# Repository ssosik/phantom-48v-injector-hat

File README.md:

# Phantom 48V Injector HAT

A Raspberry Pi add-on board that generates **+48V phantom power** from the Pi's 5V GPIO rail and
injects it onto two balanced microphone lines feeding a **HiFiBerry DAC2 ADC Pro**. It was designed
for a stereo wildlife-recording rig (Pi 4B + HiFiBerry + ESP P93 preamps with Primo EM272 capsules)
but works for any pair of P48 mics into that ADC.

| Top (3D render) | Bottom (3D render) |
|---|---|
|  |  |

> **Status: v2 (2026-10-29). Design complete, not yet fabricated or tested.** Read
> [Known issues](#known-issues) before ordering boards: items 1–3 are open design questions.

## Specs

| | |
|---|---|
| Input | 5V from Pi GPIO pins 2/4, through a π input filter (C6/C8 – L2 – C1) |
| Converter | Analog Devices LT8362 boost, 404 kHz, Burst + spread-spectrum (SSFM) mode |
| Output | 47.6 V typ (46.0–49.3 V worst case), within IEC 61938 P48 (48 V ± 4 V) |
| Load budget | 16 mA at 48 V → ~185 mA from the Pi 5V rail |
| Injection | 6.81 kΩ 0.1% per leg, 2 channels, one SPDT switch for both, green LED indicator |
| DC block | 2.2 µF / 100 V X7R per leg (~15 Hz corner after DC-bias derating) |
| Connectors | J1 2×20 GPIO socket (bottom side), J2 2×3 to HiFiBerry J4, J3/J4 1×3 XLR pigtails |
| Board | 65 × 45 mm, 2-layer, 2× M2.5 mounting holes, all SMD passives 0805 or larger |

```
Pi 5V ─► π filter ─► LT8362 boost ─► FB1 + output caps ─► SW1 ─► 6.81k ×4 ─► XLR pins 2/3 (J3, J4)
                                                                                  │
                                                     HiFiBerry J4 (J2) ◄─ 2.2µF ×4 ┘
```

See [DESIGN_DOC.md](DESIGN_DOC.md) for the full rationale: why it's non-isolated, why 400 kHz,
resistor matching and CMRR, layout strategy, and hand-assembly and first-power procedures.

## Known issues

Items 1–3 are deferred design questions. Resolve them before fabrication; [TODO.md](TODO.md)
tracks them with the remaining verification steps.

1. **Phantom switching transients reach the HiFiBerry inputs.** The DC-block caps C13–C16
   start uncharged. When SW1 switches phantom on, the ADC side of each cap jumps with the line
   side. A rough estimate (6.81 kΩ feed into the PCM1863's ~8 kΩ input) gives about +26 V
   common-mode at the input pins, decaying with τ ≈ 30 ms. Switching off gives the mirror image
   (≈ −26 V); the active drain to GND doesn't prevent it. Typical mic-preamp phantom inputs put
   clamp diodes and a series resistor after the DC-block cap for this reason. Whether the
   HiFiBerry DAC2 ADC Pro already protects its inputs hasn't been checked. Until it is, switch
   phantom only with the ADC unpowered, or add a clamp per leg (series R + BAV99 to the rails,
   or a low-capacitance TVS). See PLAN #36.
2. **Stack order is undecided.** DESIGN_DOC says Pi → HiFiBerry → this HAT. PLAN #1 says
   Pi → this HAT → HiFiBerry. J1 is a bottom-side socket with no pass-through pins, so in the
   PLAN #1 order the HiFiBerry would get no GPIO (I²S/I²C). In the DESIGN_DOC order the J1 socket
   needs male pins on the HiFiBerry to mate with. Confirm the stack physically before ordering. See PLAN #37.
3. **J2 orientation.** J2 is a top-side vertical header (PLAN #7 asked for bottom side). If it
   connects to the HiFiBerry J4 through a 2×3 IDC ribbon, the ribbon swaps the odd and even rows.
   Check the pin-1 mapping end to end, since this is the only thing keeping L/R polarity right. See PLAN #38.
4. **Schematic is label-only.** Connectivity is generated by `wire_schematic.py` as net labels
   on unwired symbols. It is correct (ERC 0 errors), and v2 hides the footprint, datasheet and
   description fields, but it still reads as a parts list rather than a circuit diagram.
5. **SW1 slide direction isn't marked.** The silkscreen labels the switch "P48" and the LED
   "ON" rather than marking ON/OFF ends, because which slider position connects the
   common to pin 1 hasn't been verified against the C&K datasheet.

## Repository layout

| Path | What |
|---|---|
| `phantom-injector-hat.kicad_pro/.kicad_sch/.kicad_pcb` | KiCad 10 project |
| `phantom-injector-hat.kicad_dru` | Custom DRC rules (MSOP-16 clearance, power widths, SW-node isolation) |
| `BOM.csv` | Authoritative BOM with manufacturer and DigiKey part numbers |
| `digikey-order-5units.csv` | DigiKey bulk-order upload for 5 boards (+ spares) |
| `DESIGN_DOC.md` | Architecture, BOM rationale, netlist, layout and assembly notes |
| `PLAN.md` | Numbered design-review log (✅ = closed) |
| `TODO.md` | Open items before fabrication |
| `make_fab.sh` | DRC gate, then Gerbers, drill, pick-and-place and BOM into `fab/` |
| `ROUTING_GUIDE.md` | Pre-routing guide: trace widths per net, loop priorities |
| `TESTS.md` | How to run DRC/ERC/netlist checks and the simulations |
| `wire_schematic.py` | Generates schematic net labels from a Python `NETLIST` dict |
| `place_components.py` | Places PCB footprints from a `PLACEMENTS` dict |
| `check_netlist.py` + `netlist_golden.json` | Detects PCB net drift against a saved golden |
| `sims/` | ngspice decks and stdlib-Python models (boost, input filter, audio path) |
| `phantom-injector-hat.pretty/` | Project footprint library: LT8362 MSOP-16-EP (`MSE_16A_ADI`, from Ultra Librarian) and the `Logo_Sosik` silkscreen logo |
| `logo.kicad_sym` | Logo as a schematic symbol (source for the footprint) |
| `DRC.rpt`, `ERC.rpt` | Latest check reports |

`phantom-injector-hat-BOM.xlsx` is an early (2026-05-12) BOM snapshot. Use `BOM.csv`.

## Working with the project

Requires KiCad 10. The Python scripts need KiCad's bundled interpreter, which provides `pcbnew`.
The paths below are for macOS:

```bash
KPY=/Applications/KiCad/KiCad.app/Contents/Frameworks/Python.framework/Versions/3.9/bin/python3
KCLI=/Applications/KiCad/KiCad.app/Contents/MacOS/kicad-cli

$KCLI pcb drc --format report --all-track-errors -o DRC.rpt phantom-injector-hat.kicad_pcb
$KCLI sch erc -o ERC.rpt phantom-injector-hat.kicad_sch
$KPY check_netlist.py
```

Current baseline: DRC 0 violations and 0 unconnected (one `track_width` exception is excluded
in the project file, with its reason); ERC 0 errors and 13 warnings, all from the vendor
symbol's pin types. See [TESTS.md](TESTS.md).

## Ordering and assembly

- `./make_fab.sh` runs DRC with schematic parity, then writes `fab/phantom-injector-hat-v2-gerbers.zip`
  (Gerbers + Excellon), `fab/phantom-injector-hat-pos.csv` and a BOM copy. `fab/` is gitignored.
- `BOM.csv` is the source of truth. L1 (Coilcraft XAL5050-223MEC) isn't stocked at DigiKey;
  order it from coilcraft.com.
- DESIGN_DOC §5.8 covers hot-plate reflow (recommended), hot-air, and iron-only assembly, plus a
  current-limited first-power test sequence.

Datasheets (not committed, since they're vendor copyright):
- [LT8362, Analog Devices](https://www.analog.com/en/products/lt8362.html)
- [C&K OS102011MA1QN1 slide switch](https://www.digikey.com/en/products/detail/c-k/OS102011MA1QN1/1981430)
- [HiFiBerry DAC2 ADC Pro](https://www.hifiberry.com/docs/data-sheets/datasheet-dac2-adc-pro/)

## Safety

48 V phantom can damage some ribbon microphones and unbalanced sources. Switch phantom off before
connecting or disconnecting mics. The boost converter has no output short-circuit protection: in a
boost topology a shorted output pulls current from the Pi's 5V rail through L1 and D1.

## License

Copyright 2026 Steve Sosik. Hardware design files, documentation and scripts are licensed under the
[CERN Open Hardware Licence Version 2 – Permissive](LICENSE) (CERN-OHL-P-2.0).

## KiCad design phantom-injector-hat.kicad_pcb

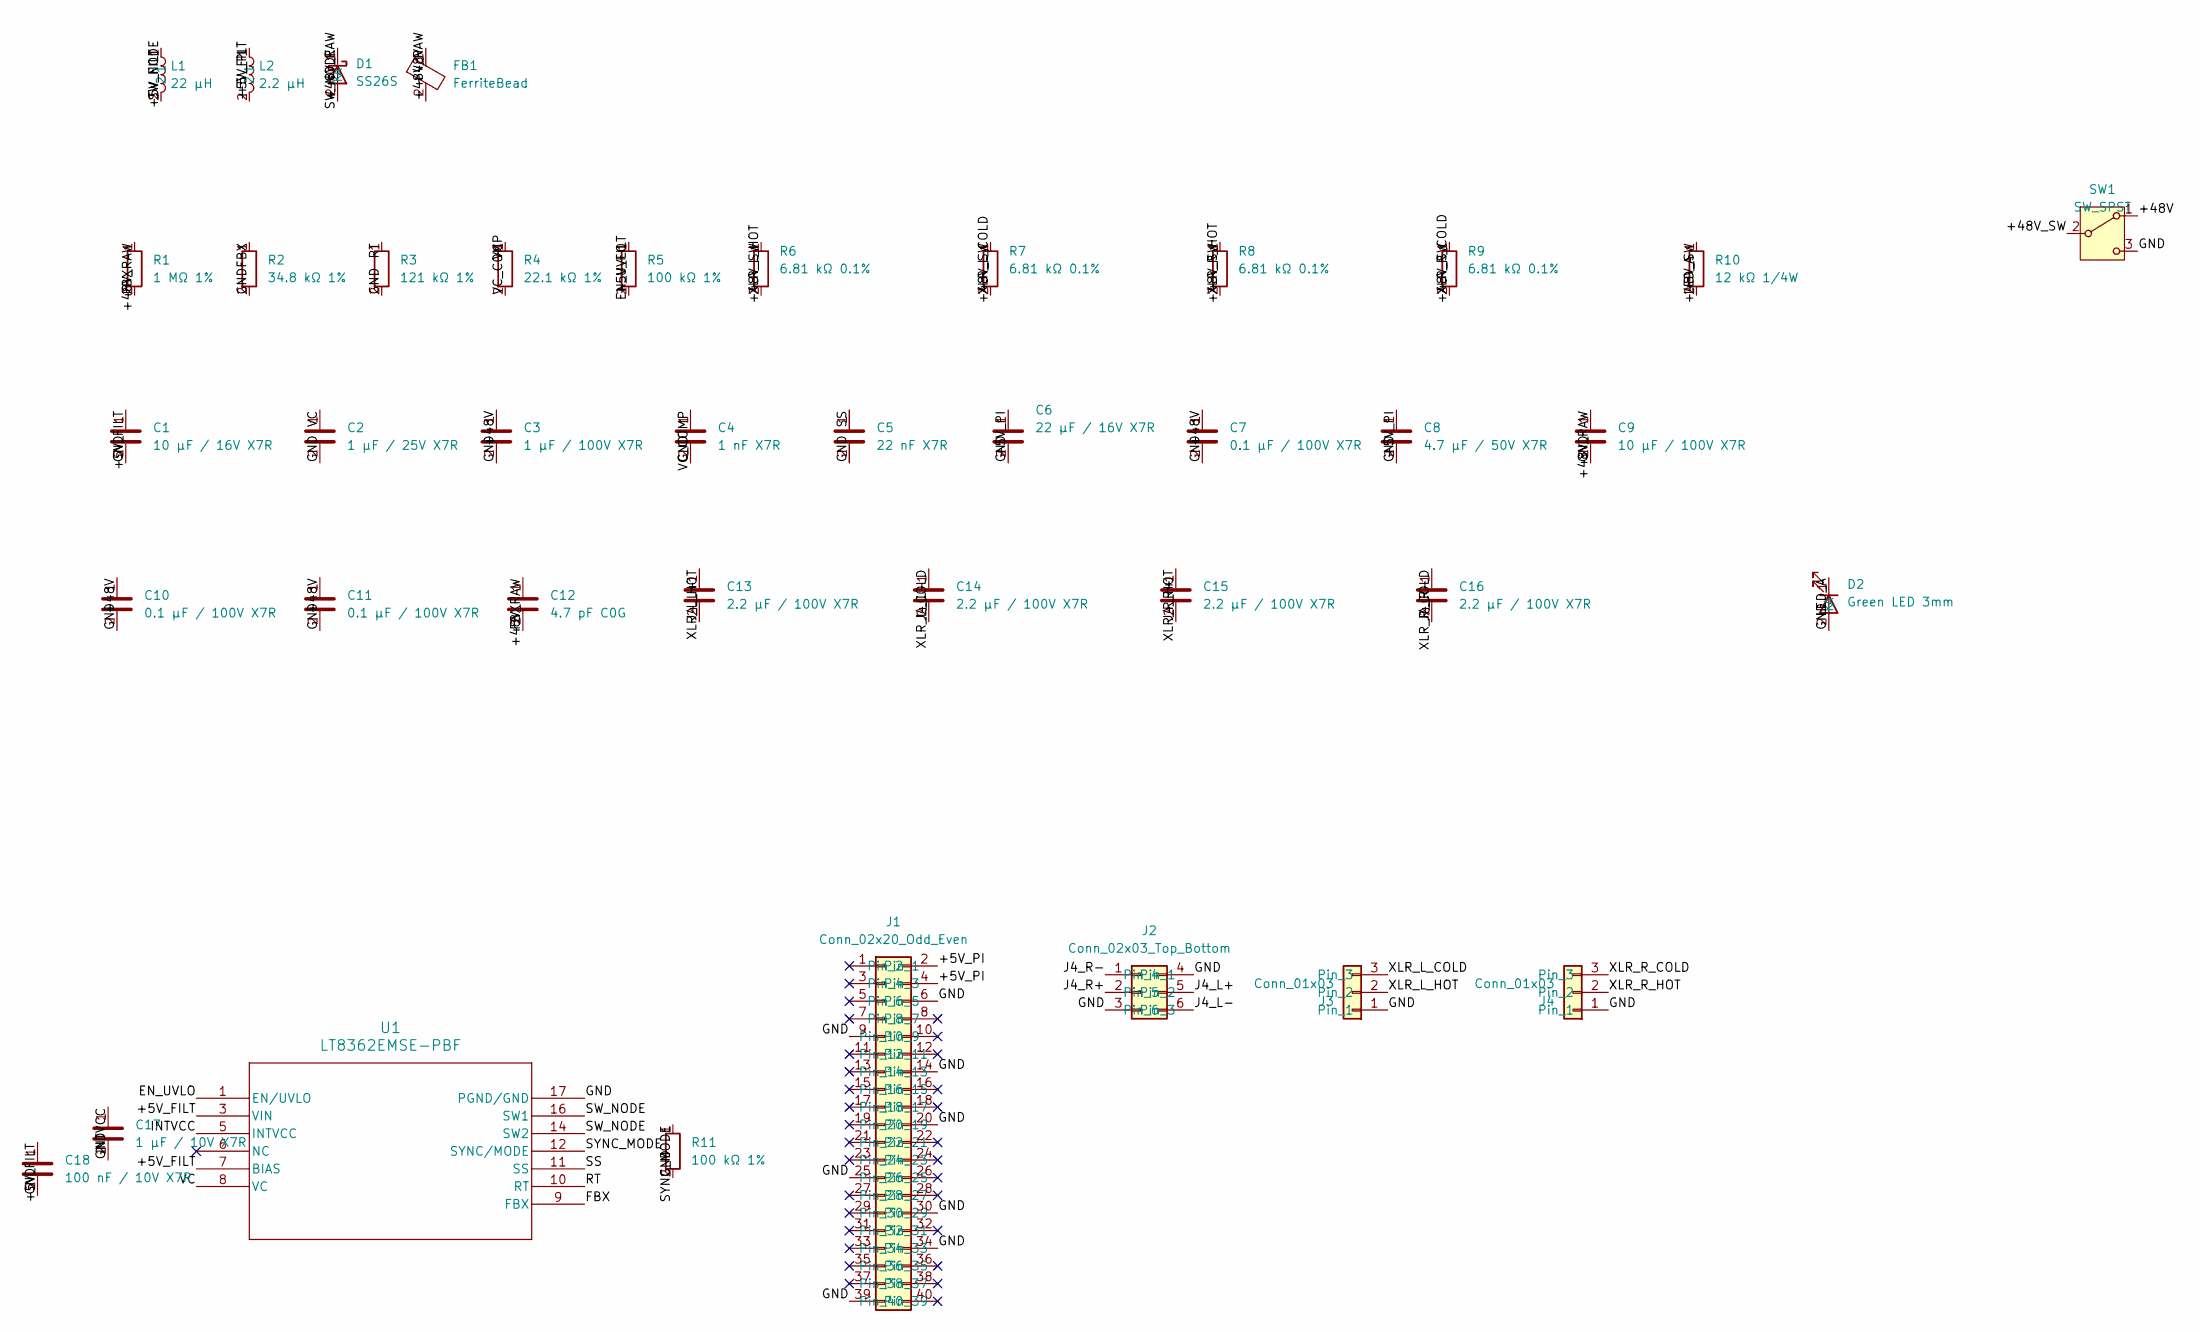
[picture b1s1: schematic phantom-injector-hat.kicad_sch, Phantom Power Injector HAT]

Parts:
C1: 10 µF / 16V X7R; C_0805_2012Metric_Pad1.18x1.45mm_HandSolder
C2: 1 µF / 25V X7R; C_0805_2012Metric_Pad1.18x1.45mm_HandSolder
C3: 1 µF / 100V X7R; C_0805_2012Metric_Pad1.18x1.45mm_HandSolder
C4: 1 nF X7R; C_0805_2012Metric_Pad1.18x1.45mm_HandSolder
C5: 22 nF X7R; C_0805_2012Metric_Pad1.18x1.45mm_HandSolder
C6: 22 µF / 16V X7R; C_1210_3225Metric_Pad1.33x2.70mm_HandSolder
C7, C10, C11: 0.1 µF / 100V X7R; C_0805_2012Metric_Pad1.18x1.45mm_HandSolder
C8: 4.7 µF / 50V X7R; C_0805_2012Metric_Pad1.18x1.45mm_HandSolder
C9: 10 µF / 100V X7R; C_1210_3225Metric_Pad1.33x2.70mm_HandSolder
C12: 4.7 pF C0G; C_0805_2012Metric_Pad1.18x1.45mm_HandSolder
C13, C14, C15, C16: 2.2 µF / 100V X7R; C_0805_2012Metric_Pad1.18x1.45mm_HandSolder
C17: 1 µF / 10V X7R; C_0805_2012Metric_Pad1.18x1.45mm_HandSolder
C18: 100 nF / 10V X7R; C_0805_2012Metric_Pad1.18x1.45mm_HandSolder
D1: SS26S; D_SMA
D2: Green LED 3mm; LED_D3.0mm
FB1: FerriteBead; L_0805_2012Metric_Pad1.05x1.20mm_HandSolder
J1: Conn_02x20_Odd_Even; PinSocket_2x20_P2.54mm_Vertical
J2: Conn_02x03_Top_Bottom; PinHeader_2x03_P2.54mm_Vertical
J3, J4: Conn_01x03; PinHeader_1x03_P2.54mm_Vertical
L1: 22 µH; L_Coilcraft_XAL5030-XXX
L2: 2.2 µH; L_Wuerth_HCI-7040
R1: 1 MΩ 1%; R_0805_2012Metric_Pad1.20x1.40mm_HandSolder
R2: 34.8 kΩ 1%; R_0805_2012Metric_Pad1.20x1.40mm_HandSolder
R3: 121 kΩ 1%; R_0805_2012Metric_Pad1.20x1.40mm_HandSolder
R4: 22.1 kΩ 1%; R_0805_2012Metric_Pad1.20x1.40mm_HandSolder
R5, R11: 100 kΩ 1%; R_0805_2012Metric_Pad1.20x1.40mm_HandSolder
R6, R7, R8, R9: 6.81 kΩ 0.1%; R_0805_2012Metric_Pad1.20x1.40mm_HandSolder
R10: 12 kΩ 1/4W; R_0805_2012Metric_Pad1.20x1.40mm_HandSolder
SW1: SW_SPST; SW_Slide_SPDT_Angled_CK_OS102011MA1Q
U1: LT8362EMSE-PBF; MSE_16A_ADI

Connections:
/+5V_FILT: C1.1, C18.1, L1.1, L2.2, R5.2, U1.3 (VIN), U1.7 (BIAS)
/+5V_PI: C6.1, C8.1, J1.2, J1.4, L2.1
/+48V: C3.1, C7.1, C10.1, C11.1, FB1.1, SW1.1 (A)
/+48V_RAW: C9.1, C12.1, D1.2 (A), FB1.2, R1.1
/+48V_SW: R6.1, R7.1, R8.1, R9.1, R10.1, SW1.2 (B)
/EN_UVLO: R5.1, U1.1 (EN/UVLO)
/FBX: C12.2, R1.2, R2.1, U1.9 (FBX)
/GND: C1.2, C2.2, C3.2, C4.2, C5.2, C6.2, C7.2, C8.2, C9.2, C10.2, C11.2, C17.2, C18.2, D2.2 (A), J1.6, J1.9, J1.14, J1.20, J1.25, J1.30, J1.34, J1.39, J2.3, J2.4, J3.1, J4.1, R2.2, R3.2, R11.2, SW1.3 (C), U1.17 (PGND/GND)
/INTVCC: C17.1, U1.5 (INTVCC)
/J4_L+: C13.2, J2.5
/J4_L-: C14.2, J2.6
/J4_R+: C15.2, J2.2
/J4_R-: C16.2, J2.1
/LED_A: D2.1 (K), R10.2
/RT: R3.1, U1.10 (RT)
/SS: C5.1, U1.11 (SS)
/SW_NODE: D1.1 (K), L1.2, U1.14 (SW2), U1.16 (SW1)
/SYNC_MODE: R11.1, U1.12 (SYNC/MODE)
/VC: C2.1, R4.1, U1.8 (VC)
/VC_COMP: C4.1, R4.2
/XLR_L_COLD: C14.1, J3.3, R7.2
/XLR_L_HOT: C13.1, J3.2, R6.2
/XLR_R_COLD: C16.1, J4.3, R9.2
/XLR_R_HOT: C15.1, J4.2, R8.2

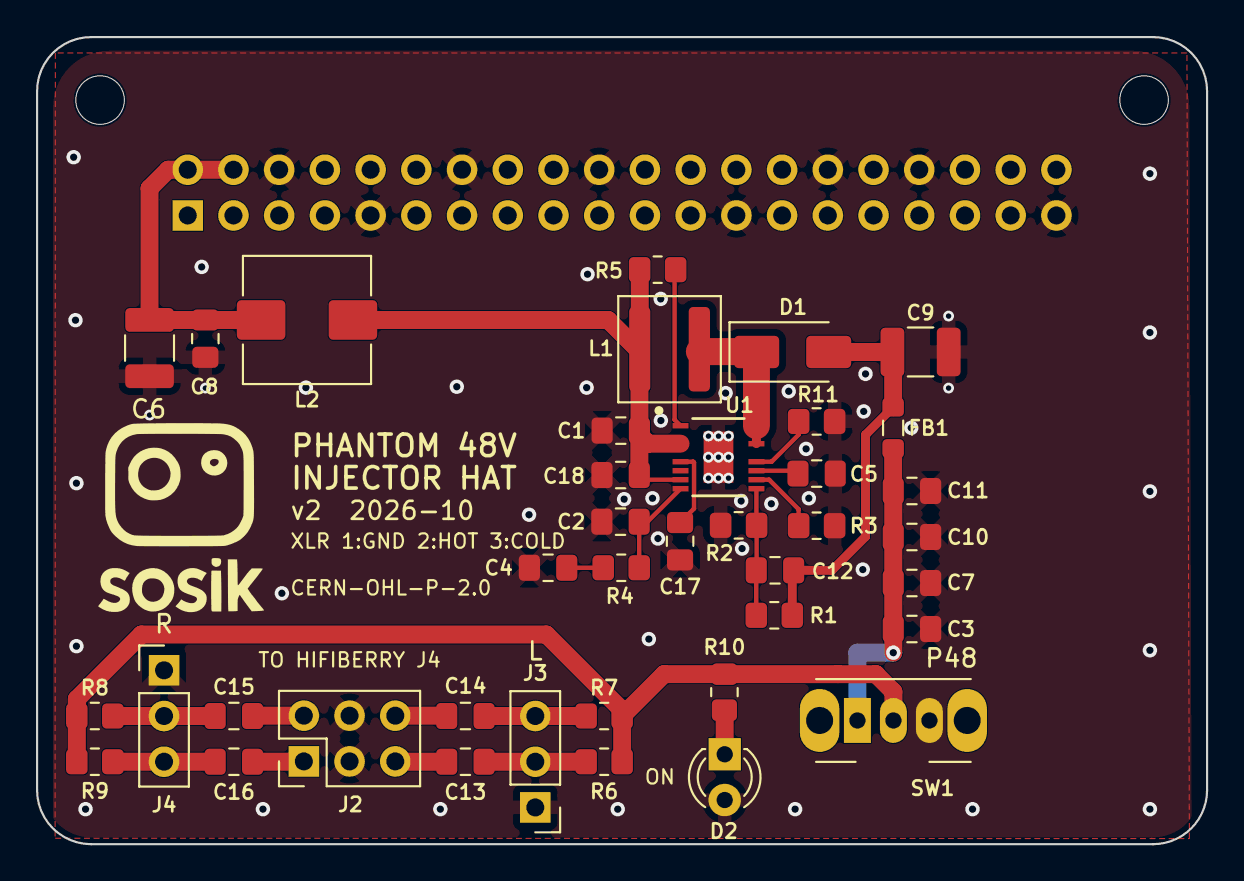
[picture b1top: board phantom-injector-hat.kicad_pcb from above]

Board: 2 copper layers, 65.0 x 44.8 mm, 43 parts (1 on the bottom side), 24 nets.

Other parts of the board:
G1: Logo_Sosik
MH1, MH2: MountingHole_2.7mm_M2.5

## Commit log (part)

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2026-05-12 Initial add
2026-05-12 Update SMD component sizes
2026-05-13 Wiring the schematic WIP
2026-05-16 Add plan
2026-05-17 Initial connections complete
2026-05-19 smaller label text
2026-05-20 checkpoint
2026-05-21 checkpoint before final layout and wiring
2026-05-21 Starting routing and component layout
2026-05-21 checkpointing layout and tracing
2026-05-21 Checkpoint routing
2026-05-21 checkpoint all routed and layed out
2026-05-21 mostly DRC clean
2026-05-21 Good looking layout
2026-05-30 Good checkpoint
2026-05-31 Checkpoint!
2026-06-02 fixups
2026-06-02 Chkpt
2026-06-02 CHKP
2026-06-02 Getting close
2026-06-02 Close
2026-06-03 slight reorganizing of traits
2026-06-05 working on BoM
2026-06-05 Add BOM
2026-06-05 Addsimulation files
2026-06-05 Hopefully correct locations.
2026-06-13 Adding bulk upload CSV for digikey
2026-06-13 Updating BOMs
